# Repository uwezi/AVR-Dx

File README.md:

# AVR-Dx / AVR-EA
some general stuff about the AVR-DA, AVR-DB, AVR-DD and AVR-EA series

## What and Why
As I am just getting started with the "new" Microchip AVR-Dx series of microcontrollers which seem to be replacing the good old ATmega328 workhorse and its tiny and mega friends for me, I plan to collect some usefull notes here.

## Libraries:
- [DS18B20](libraries/DS18B20) - a library to use the 1-wire digital thermometer DS18B20
- [lcd](libraries/lcd) - a library for a HD44780-based alphanumeric display, based on Peter Fleury's LCD library
- [lcd_i2c](libraries/lcd_i2c) - a library to use an alphanumeric display with a serial I2C port extender board
- [modbus_rtu](libraries/modbus_rtu) - basic functionality for a RS485 Modbus/RTU slave
- [nokia5110](libraries/nokia5110) - simple library for text and graphics on a Nokia 5110 LCD with 84x48 pixels

## Hardware
- [pinouts](pinouts) - an overview over the pinouts of selected AVR-Dx chips
- [UPDI + UART](UPDI_plus_UART) - a breadbaord UPDI programmer and UART interface

- [UPDI Programmer](UPDI_programmer) - how to convert a USB-C UART module into an UPDI programmer and the attached pitfalls

## Observations and errata
- On both the AVR32DA28 and AVR128DA64, purchased in summer 2025, the RESET pin was disabled in the `syscfg0` fuse register by default. This is in contrast to the corresponding section from both devices' datasheets. The value in the fuse register on both factory-new devices was `0xC0` and not `0xC8`. 
> The default value given in this fuse description is the factory-programmed value, and should not be mistaken for the
Reset value.

Setting the fuse to the correct value for enabling the reset pin can be done by
```avrdude -p32da28 -PCOM3 -cserialupdi -U syscfg0:w:0xc0:m```

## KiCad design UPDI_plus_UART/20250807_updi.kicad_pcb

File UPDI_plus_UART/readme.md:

# UPDI
The new AVR chips use a single-wire serial programming interface UPDI. There are plenty of sources on the web on how to build an avrdude-compatible programmer
using just a standard USB-UART TTL dongle.

But now I took the general idea of my USBasp clone which I had developed for my students about 10 years ago, where the programmer snaps onto the breadboard and 
automatically provides power to the breadboard's side rails as well. As usual I let [PCBgogo](https://www.pcbgogo.com/) manufacture my 2-layer boards and was very satisfied 
with their services.

The design uses the lesser known [CH342K](https://docs.sparkfun.com/SparkFun_RTK_Postcard/assets/component_documentation/CH342%20Datasheet.pdf) 
which can be sourced from LCSC and Aliexpress for about € 1,50 a piece - I found no "western" source for this chip. The chip is similar to the 
CH340-series of USB-UARTs, but it even contains two independent serial ports in a single 10pin SMD package with an exposed pad on the underside, it needs no external oscillator and
it seems to be already supported by all modern operating systems.

## KiCAD 3D rendering

## KiCAD view of both front and back layer

## BOM
| Part | Package | Count | Designators | Comment |
|------|---------|-------|-------------|---------|
| 100 nF, ceramic, 15 V | 0805 | 4 | C3, C4, C5, C6 | standard component, e.g. LCSC C519981 |
| 1 µF, ceramic, 25 V   | 0805 | 2 | C1, C2 | standard component, e.g. LCSC C91186 |
| 1 kΩ, ±1%, 250 mW, 1k0        | 0805 | 4 | R4, R5, R6, R7 | standard component, e.g LCSC C6681310 |
| 470 Ω, ±1%, 250 mW, 470R      | 0805 | 1 | R1 | standard component, e.g. LCSC C5120103 |
| 5.1 kΩ, ±1%, 125 mW, 5k1      | 0805 | 2 | R2, R3 | standard component, e.g. LCSC C2907269 |
| LED red               | 0805 | 1 | D7 | standard component, e.g. LCSC C965812 |
| LED blue              | 0805 | 1 | D6 | standard component, e.g. LCSC C965817 |
| LED green             | 0805 | 1 | D5 | standard component, e.g. LCSC C84260 |
| LED yellow            | 0805 | 1 | D4 | standard component, e.g. LCSC C965814 |
| BAT54W                | SOT-323 | 1 | D1 | LCSC C41374260 |
| polyfuse 1A, 16 V     | 1812 | 1 | F1 | eg BSMD1812-110-24V LCSC C883149 |
| AMS1117-33            | SOT-223-3 | 1 | U2 | or similar LCSC C426566 |
| CH342K                | SSOP-10-1EP | 1 | U1 | LCSC C2826608 |
| pin socket 3-pin      | 2.54 mm | 2 | J6, J8 | e.g. LCSC C541850 |
| pin header 3-pin      | 2.54 mm | 1 | J7 | e.g. LCSC C41425293 |
| USB-C receptacle      | USB4105 | 1 | J1 | GCT or similar, e.g. LCSC C2765186 |
| pin header 2-pin      | 2.54 mm | 4 | J2, J3, J4, J5 | e.g. LCSC C492401 |

(the references to [LCSC](https://www.lcsc.com/) part numbers are just suggestions, apart from the CH342K none of the components is critical and can be replaced by any number of compatible components from other sources)

## interactive BOM
[generated by the interactive BOM KiCAD plugin](https://html-preview.github.io/?url=https://github.com/uwezi/AVR-Dx/raw/refs/heads/main/UPDI_plus_UART/ibom.html)

# Files
You can find the KiCAD and gerber files in this directory.

There is also an OpenSCAD design and .stl files for a case for the programmer when you do not intend to use it on a breadbaord.

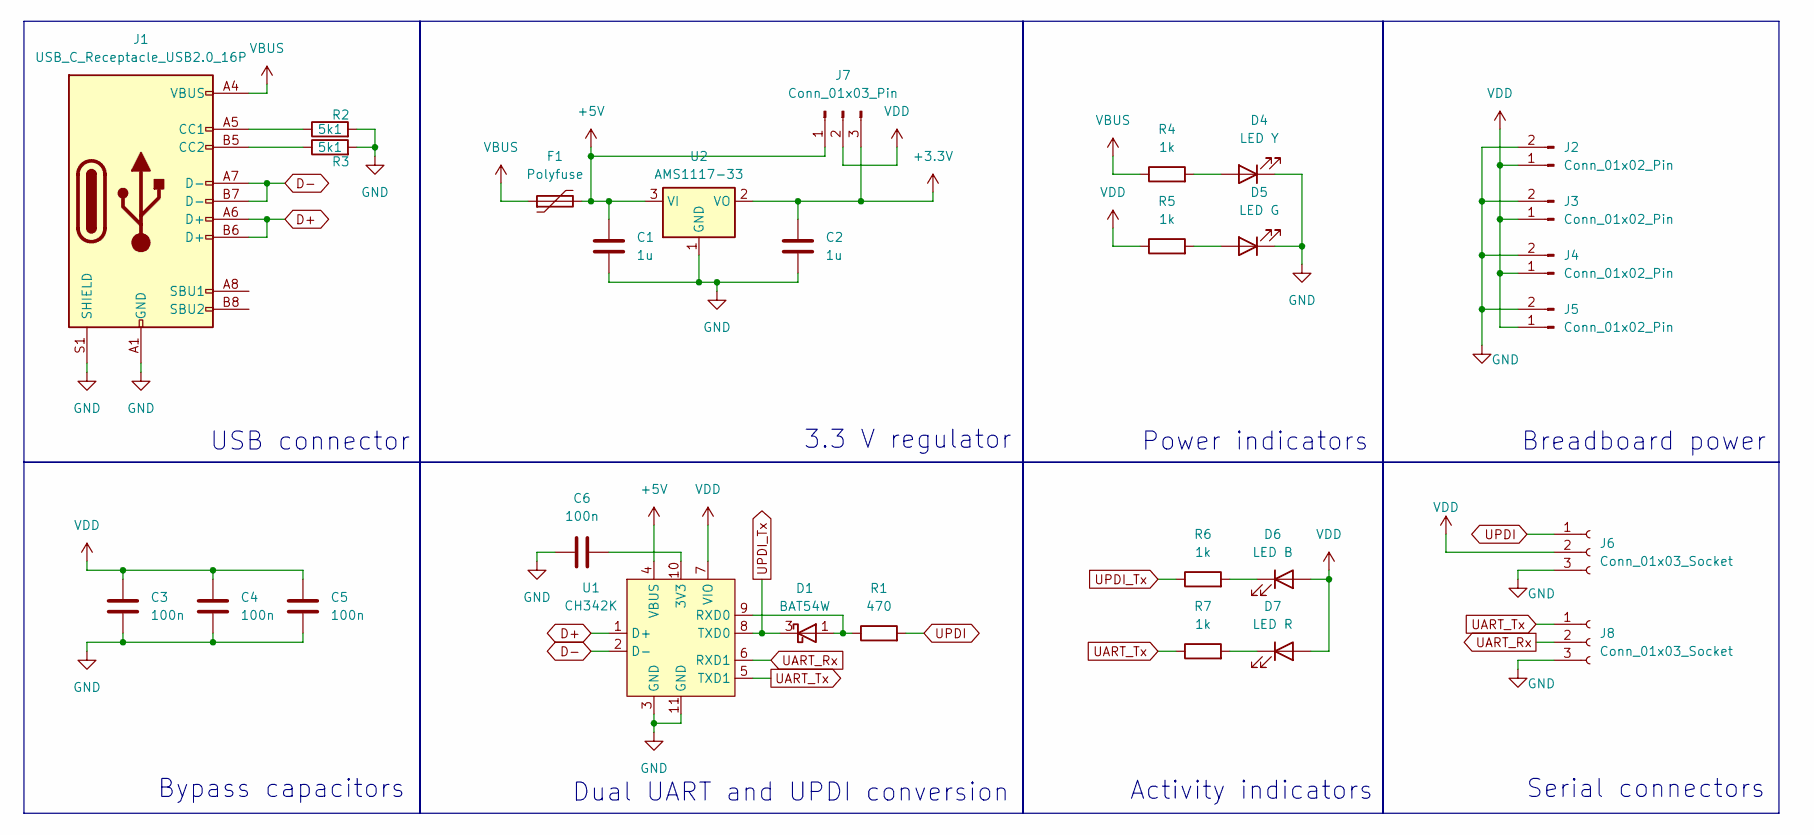
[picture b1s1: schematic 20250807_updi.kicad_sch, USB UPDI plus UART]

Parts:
C1, C2: 1u; C_0805_2012Metric_Pad1.18x1.45mm_HandSolder; LCSC C91186
C3, C4, C5, C6: 100n; C_0805_2012Metric_Pad1.18x1.45mm_HandSolder; LCSC C519981
D1: BAT54W; SOT-323_SC-70; LCSC C41374260
D4: LED Y; LED_0805_2012Metric_Pad1.15x1.40mm_HandSolder; LCSC C965814
D5: LED G; LED_0805_2012Metric_Pad1.15x1.40mm_HandSolder; LCSC C84260
D6: LED B; LED_0805_2012Metric_Pad1.15x1.40mm_HandSolder; LCSC C965817
D7: LED R; LED_0805_2012Metric_Pad1.15x1.40mm_HandSolder; LCSC C965812
F1: Polyfuse; Fuse_1812_4532Metric_Pad1.30x3.40mm_HandSolder; LCSC C883149
J1: USB_C_Receptacle_USB2.0_16P; USB_C_Receptacle_GCT_USB4105-xx-A_16P_TopMnt_Horizontal; LCSC C2765186
J2, J3, J4, J5: Conn_01x02_Pin; PinHeader_1x02_P2.54mm_Vertical; LCSC C492401
J6, J8: Conn_01x03_Socket; PinSocket_1x03_P2.54mm_Vertical; LCSC C541850
J7: Conn_01x03_Pin; PinHeader_1x03_P2.54mm_Vertical; LCSC C41425293
R1: 470; R_0805_2012Metric_Pad1.20x1.40mm_HandSolder; LCSC C5120103
R2, R3: 5k1; R_0805_2012Metric_Pad1.20x1.40mm_HandSolder; LCSC C2907269
R4, R5, R6, R7: 1k; R_0805_2012Metric_Pad1.20x1.40mm_HandSolder; LCSC C6681310
U1: CH342K; SSOP-10-1EP_3.9x4.9mm_P1mm_EP2.1x3.3mm; LCSC C2826608
U2: AMS1117-33; SOT-223-3_TabPin2; LCSC C426566

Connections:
+3.3V: C2.1, J7.3, U2.2 (VO)
+5V: C1.1, F1.2, J7.1, U1.4 (VBUS), U2.3 (VI)
D+: J1.A6 (D+), J1.B6 (D+), U1.1 (D+)
D-: J1.A7 (D-), J1.B7 (D-), U1.2 (D-)
GND: C1.2, C2.2, C3.2, C4.2, C5.2, C6.1, D4.1 (K), D5.1 (K), J1.A1 (GND), J1.A12 (GND), J1.B1 (GND), J1.B12 (GND), J1.S1 (SHIELD), J2.2, J3.2, J4.2, J5.2, J6.3, J8.3, R2.2, R3.2, U1.3 (GND), U1.11 (GND), U2.1 (GND)
unnamed: D1.1 (A), R1.1, U1.9 (RXD0)
unnamed: D4.2 (A), R4.2
unnamed: D5.2 (A), R5.2
unnamed: D6.1 (K), R6.2
unnamed: D7.1 (K), R7.2
unnamed: J1.A5 (CC1), R2.1
unnamed: J1.B5 (CC2), R3.1
unnamed: C6.2, U1.10 (3V3)
UART_Rx: J8.2, U1.6 (RXD1)
UART_Tx: J8.1, R7.1, U1.5 (TXD1)
UPDI: J6.1, R1.2
UPDI_Tx: D1.3 (K), R6.1, U1.8 (TXD0)
VBUS: F1.1, J1.A4 (VBUS), J1.A9 (VBUS), J1.B4 (VBUS), J1.B9 (VBUS), R4.1
VDD: C3.1, C4.1, C5.1, D6.2 (A), D7.2 (A), J2.1, J3.1, J4.1, J5.1, J6.2, J7.2, R5.1, U1.7 (VIO)

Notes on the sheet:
USB connector
Activity indicators
Power indicators
Bypass capacitors
Breadboard power
Dual UART and UPDI conversion
Serial connectors
3.3 V regulator

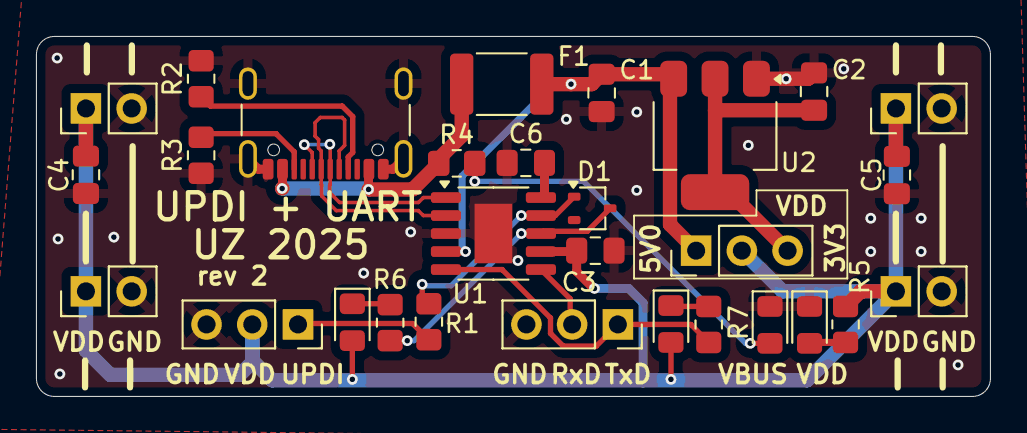
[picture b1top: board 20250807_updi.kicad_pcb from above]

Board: 2 copper layers, 53.0 x 20.0 mm, 29 parts (0 on the bottom side), 19 nets.

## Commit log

2025-06-29 Add files via upload
    fixed typo UDPI -> UPDI
2025-07-02 added AVR-EA
2025-07-11 Create LICENSE
2025-07-11 added change of configuration
    I added a function to write the 3 scratchpad bytes for the configuration of the alarm temperatures and the resolution
2025-07-16 Add files via upload
    adopted commenting to doxygen standard
2025-08-08 Update platformio.ini
    removed the link to the Arduino framework and instead added a reference to the 3.7 version of the avr-gcc toolchain
2025-10-20 Add files via upload
    - added a tiny font on a 4x6 raster allowing for 21 horizontal characters and 8 rows (14 characters and 6 rows with the standard font)
    - added an example `main.c` which can be used to find the optimum contrast setting `VOP`
    - breaking changes:
    - - `NOKIA_print_p` becomes `NOKIA_print_P` as for the standard string functions
    - - font files are now true `.h` header files rather then weird includes
2025-11-16 Add files via upload
    cleaned up schematics and added LCSC part numbers
